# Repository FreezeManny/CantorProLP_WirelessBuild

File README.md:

# My Custom Cantor Pro LP Wireless Keyboard

This repository contains all the files and configuration for my personal build of the **Cantor Pro LP**, a 40% low-profile, hotswap, split ergonomic keyboard. This build is fully wireless, using Nice!Nano controllers running the ZMK firmware.

## Table of Contents

- [Hardware Components](#hardware-components)
- [PCB](#pcb)
- [Firmware (ZMK)](#firmware-zmk)
- [3D Printed Case](#3d-printed-case)
- [Build Notes](#build-notes)
- [Acknowledgements](#acknowledgements)

---

## Hardware Components

| Component | Item | Notes |
| :--- | :--- | :--- |
| **Keyboard Kit** | PCBs ordered from JLCPCB but | A kit can be sorced from 42. Keebs: [Cantor Pro LP Kit](https://42keebs.eu/shop/kits/pro-micro-based/cantor-pro-lp-40-low-profile-hotswap-split-ergo-kit/) |
| **Small Electronics** | 2x Push Button 6x2mm & 42x Kailh Choc V1 Hotswap Sockets | Ordered from aliExpress, not needed when buying a Kit |
| **Small Case Parts**| 4x M3 Heat insert, 4x M3 Screw | needed for securing PCB to case |
| **Controllers** | 2x Nice!Nano v2 (or alternative) | For wireless connectivity via Bluetooth. |
| **Batteries** | 2x 102050 LiPo (1000mAh) | One for each half. Fits perfectly with the custom case. |
| **Switches** | 42x Kailh Choc V1  | in my case: Sunset, waiting for sunrise |
| **Keycaps** | 42x Choc V1 Keycaps` | e.g., MBK Blank Choc Keycaps. |
| **Case** | Custom 3D Printed Case & Cover | Files are located in the `/case` directory. |

---
## PCB
The 42 Keebs Cantor was remixed to change the text of the keyboard and understand the layers. 
The Files are located in the `/pcb/` directory. 

## Firmware (ZMK)

This keyboard runs on the [ZMK Firmware](https://zmk.dev/docs), which is designed for wireless keyboards. 

### My Configuration

* **ZMK Config:** The main configuration files are located in the `/config/` directory.

### Configure, Build & Flash
* Configuration: Done using awesome [Keymap Editor](https://nickcoutsos.github.io/keymap-editor/)
* Build: standard Github Actions
* Flash: To Flash consult Microcontroller Documentation

---

## 3D Printed Case

This build uses a custom-designed 3D printed case and a friction fit travel cover to protect the keys.
It was built in Fusion360 and source files, as well as Step files are shared. (because STL sucks)
* **Files Location:** `/case`

Only one side is provided. To print the other half, mirror the files in the slicer. 

### Recommended Print Settings

* **Material:** Any, preferabbly in ABS/ASA/PETG due to better heat resistance
* **Outer Walls:** minimum of 3
* **Layer Height:** 0.2mm
* **Infill:** 15-20%
* **Supports:** Not required

---

## Build Notes

* **Fully Wireless:** This build is fully wireless and does **not** use a TRRS cable. The two halves communicate via Bluetooth. The TRRS jacks on the PCB are not installed.
* **Battery Placement:** The batteries are not placed underneath the controllers. They are placed under in the Case. Due to tight tolerances, trim the PCB pins flush
* **Pin Difficultys using NiceNano:** Due to the design of the PCB, when using the NiceNano, the 101 Pin has to be connected to the bottom row at an angle. Also on the right side of the keyboard, the left thumb key and the 5. key in Row 3 are swapped in the keymap. 

---

## Acknowledgements

* **Cantor Keyboard:** Diego Palacios
* **Cantor Pro LP Kit:** [42. Keebs](https://42keebs.eu/)
* **ZMK Firmware:** The ZMK contributors.

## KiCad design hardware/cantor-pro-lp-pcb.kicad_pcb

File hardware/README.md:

# Cantor Pro LP Keyboard

Cantor Pro LP (formerly known as Cantor Pro Frood) is based on the original Cantor Keyboard by Diego Palacios, with the following modifications:

* Supports more modern controllers instead of the Black Pill:
    * [42. Keebs Frood](https://42keebs.eu/shop/parts/controllers/frood-rp2040-pro-micro-controller/) ([GitHub repository](https://github.com/piit79/Frood)) RP2040-based controller
    * [nice!nano](https://nicekeyboards.com/nice-nano/) controller for a **wireless build**
* Adds battery contacts and a power switch
* It is a bit narrower thanks to the smaller controller
* Uses Kailh Choc V1 hotswap sockets
* Supports RGB underglow using 6x WS2812B / SK6812 5050 RGB modules
* Has holes for standoffs for use with a PCB switch plate or a [layered acrylic case](https://github.com/piit79/cantor/tree/main/case/cantor-pro-lp)

Cantor Pro LP kit is available for purchase at [42. Keebs](https://42keebs.eu/shop/kits/pro-micro-based/cantor-pro-lp-40-low-profile-hotswap-split-ergo-kit/).

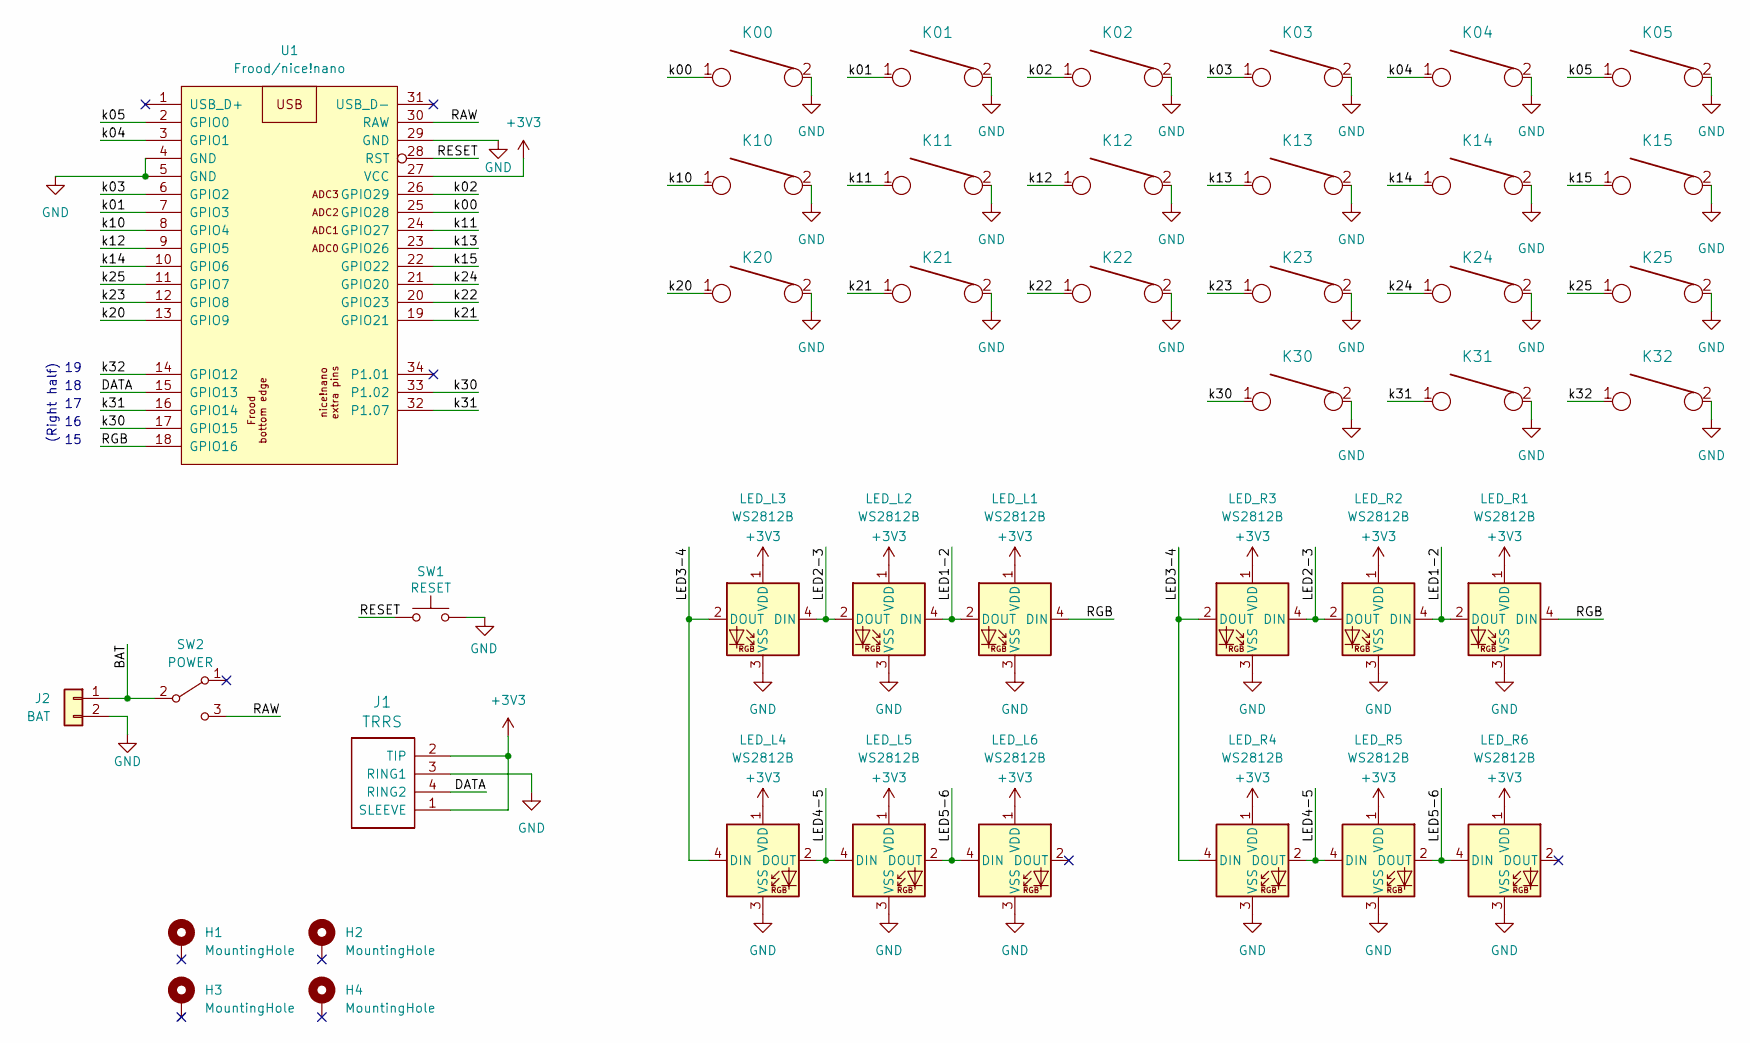
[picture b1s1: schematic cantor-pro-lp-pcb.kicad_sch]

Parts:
H1, H2, H3, H4: MountingHole; Standoff_Hole
J1: TRRS; TRRS-PJ-320A-reversible-symmetric
J2: BAT; ProMicro_Battery_Connector_Double_Sided_wide
K00, K01, K02, K03, K04, K05, K10, K11, K12, K13, K14, K15, K20, K21, K22, K23, K24, K25, K30, K31, K32: KEYSW; Kailh_socket_PG1350_reversible_cropped_pads_rounded_cutouts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
LED_L1, LED_L2, LED_L3, LED_L4, LED_L5, LED_L6: WS2812B; LED_WS2812B_PLCC4_5.0x5.0mm_P3.2mm_w_cutout
LED_R1, LED_R2, LED_R3, LED_R4, LED_R5, LED_R6: WS2812B; LED_WS2812B_PLCC4_5.0x5.0mm_P3.2mm_w_cutout
SW1: RESET; TACT_SWITCH_TVBP06
SW2: POWER; SW_SPDT_PCM12_double_sided_shifted_with_edge_cutouts
U1: Frood/nice!nano; Frood_nice-nano_PinHeader_2x12+5+3_P2.54mm_Dual_V-aligned

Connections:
+3V3: J1.1 (SLEEVE), J1.2 (TIP), LED_L1.1 (VDD), LED_L2.1 (VDD), LED_L3.1 (VDD), LED_L4.1 (VDD), LED_L5.1 (VDD), LED_L6.1 (VDD), LED_R1.1 (VDD), LED_R2.1 (VDD), LED_R3.1 (VDD), LED_R4.1 (VDD), LED_R5.1 (VDD), LED_R6.1 (VDD), U1.27 (VCC)
/BAT: J2.1, SW2.2 (B)
/DATA: J1.4 (RING2), U1.15 (GPIO13)
/LED1-2: LED_L1.2 (DOUT), LED_L2.4 (DIN), LED_R1.2 (DOUT), LED_R2.4 (DIN)
/LED2-3: LED_L2.2 (DOUT), LED_L3.4 (DIN), LED_R2.2 (DOUT), LED_R3.4 (DIN)
/LED3-4: LED_L3.2 (DOUT), LED_L4.4 (DIN), LED_R3.2 (DOUT), LED_R4.4 (DIN)
/LED4-5: LED_L4.2 (DOUT), LED_L5.4 (DIN), LED_R4.2 (DOUT), LED_R5.4 (DIN)
/LED5-6: LED_L5.2 (DOUT), LED_L6.4 (DIN), LED_R5.2 (DOUT), LED_R6.4 (DIN)
/RAW: SW2.3 (C), U1.30 (RAW)
/RESET: SW1.2, U1.28 (RST)
/RGB: LED_L1.4 (DIN), LED_R1.4 (DIN), U1.18 (GPIO16)
/k00: K00.1, U1.25 (GPIO28)
/k01: K01.1, U1.7 (GPIO3)
/k02: K02.1, U1.26 (GPIO29)
/k03: K03.1, U1.6 (GPIO2)
/k04: K04.1, U1.3 (GPIO1)
/k05: K05.1, U1.2 (GPIO0)
/k10: K10.1, U1.8 (GPIO4)
/k11: K11.1, U1.24 (GPIO27)
/k12: K12.1, U1.9 (GPIO5)
/k13: K13.1, U1.23 (GPIO26)
/k14: K14.1, U1.10 (GPIO6)
/k15: K15.1, U1.22 (GPIO22)
/k20: K20.1, U1.13 (GPIO9)
/k21: K21.1, U1.19 (GPIO21)
/k22: K22.1, U1.20 (GPIO23)
/k23: K23.1, U1.12 (GPIO8)
/k24: K24.1, U1.21 (GPIO20)
/k25: K25.1, U1.11 (GPIO7)
/k30: K30.1, U1.17 (GPIO15), U1.33 (P1.02)
/k31: K31.1, U1.16 (GPIO14), U1.32 (P1.07)
/k32: K32.1, U1.14 (GPIO12)
GND: J1.3 (RING1), J2.2, K00.2, K01.2, K02.2, K03.2, K04.2, K05.2, K10.2, K11.2, K12.2, K13.2, K14.2, K15.2, K20.2, K21.2, K22.2, K23.2, K24.2, K25.2, K30.2, K31.2, K32.2, LED_L1.3 (VSS), LED_L2.3 (VSS), LED_L3.3 (VSS), LED_L4.3 (VSS), LED_L5.3 (VSS), LED_L6.3 (VSS), LED_R1.3 (VSS), LED_R2.3 (VSS), LED_R3.3 (VSS), LED_R4.3 (VSS), LED_R5.3 (VSS), LED_R6.3 (VSS), SW1.1, U1.4 (GND), U1.5 (GND), U1.29 (GND)

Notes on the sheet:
(Right half)

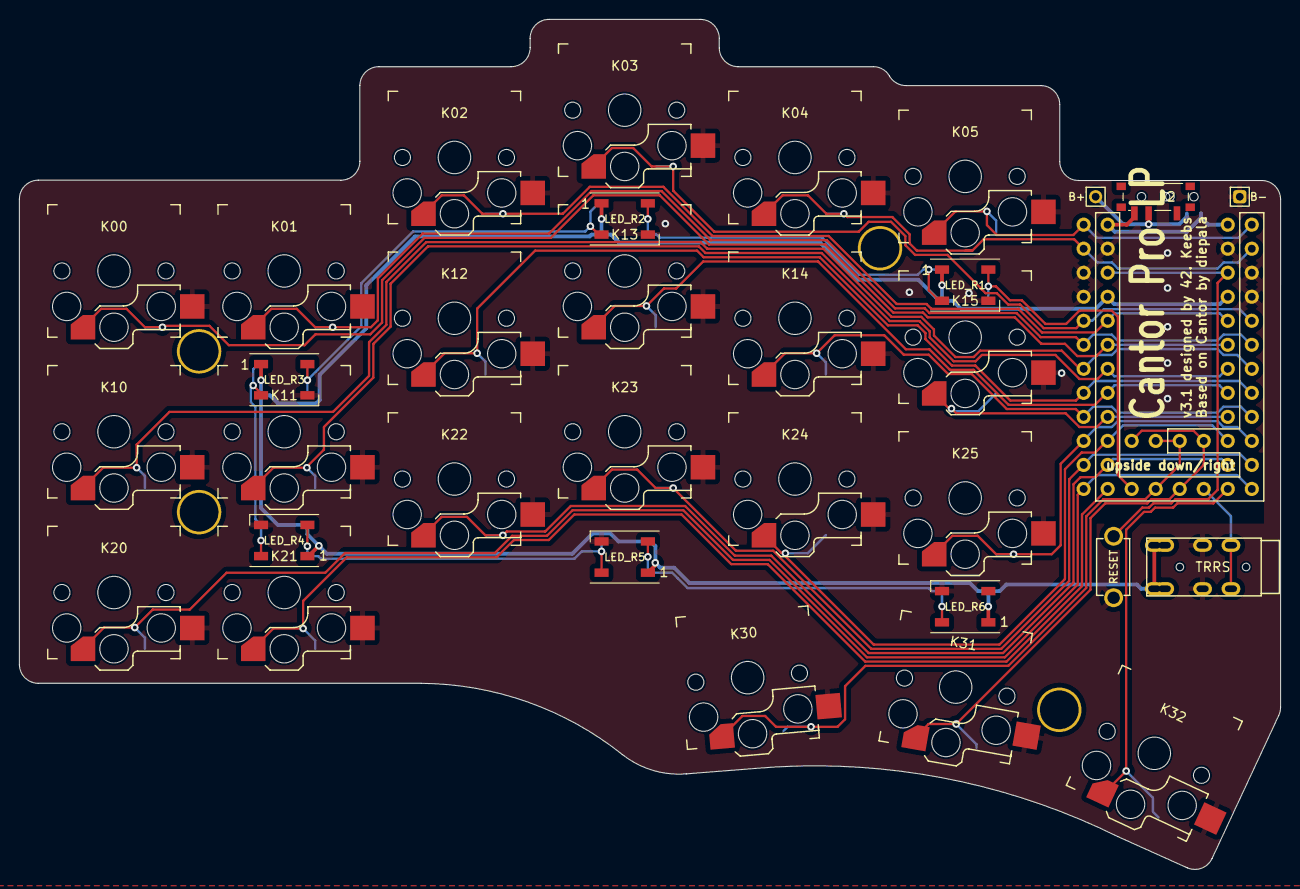
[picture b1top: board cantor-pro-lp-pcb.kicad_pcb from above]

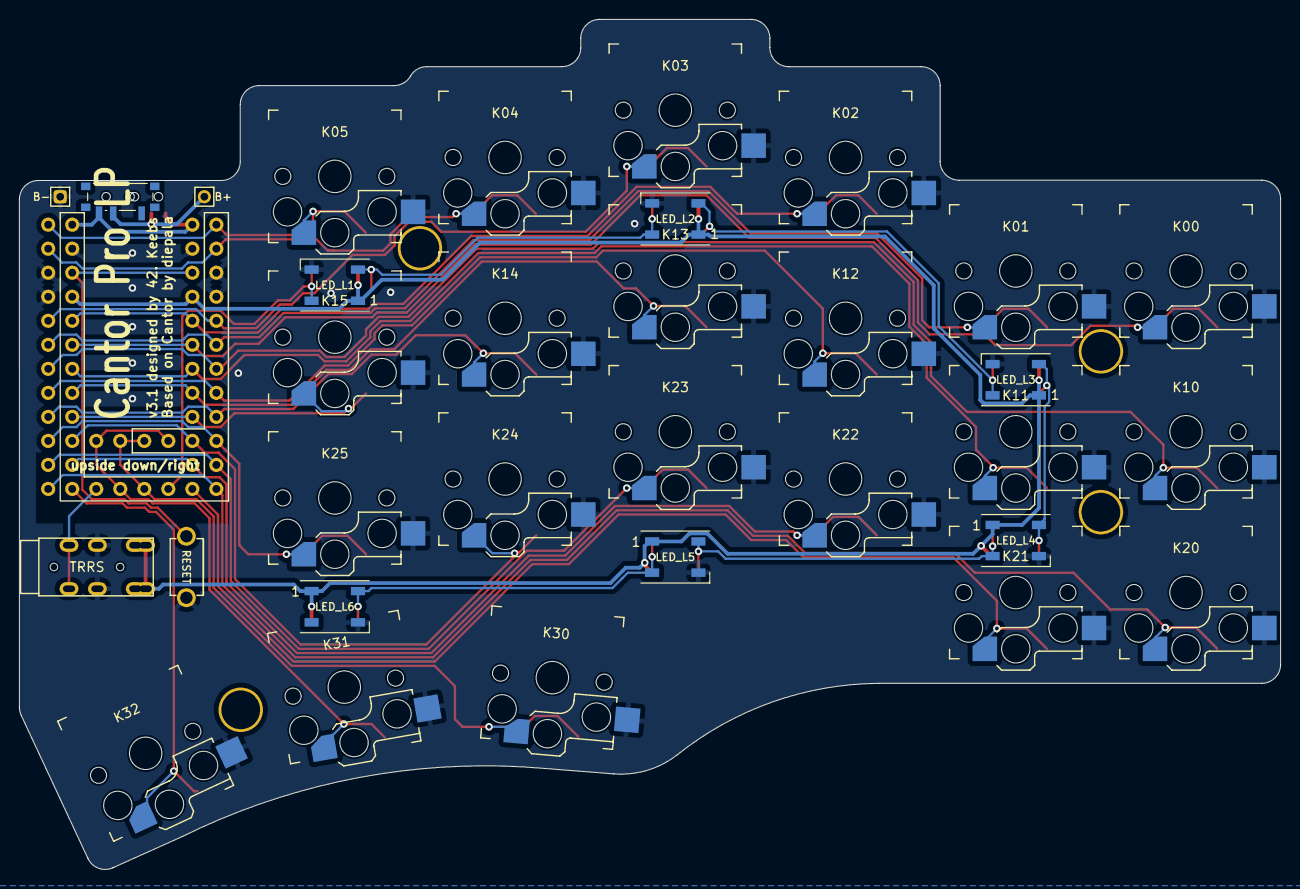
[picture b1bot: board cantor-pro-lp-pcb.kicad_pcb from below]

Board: 2 copper layers, 133.4 x 89.9 mm, 42 parts (6 on the bottom side), 33 nets.

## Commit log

2025-07-16 Initial User Config.
2025-07-24 Updated corne.keymap
2025-07-24 Added first Config Example
2025-07-24 added delete behind shift backspace
2025-08-30 Added Hardware
2025-08-31 Custom Message
2025-09-02 Updated Structure
2025-09-02 Reverse
2025-09-02 Rename back
2025-09-02 Added Caldera Default Config
2025-09-02 Added Layout Info.json
2025-09-02 Added second half
2025-09-02 Changed Info Path
2025-09-02 Updated layout and overlay. Still lots of work to do
2025-09-02 Updated Switch Map
2025-09-02 Added Correct Keyboard Switch Mapping
2025-09-02 Added KSCAN GPIOs to Layout
2025-09-02 Changed Paths to (hopefully) correct build path
2025-09-02 Moved Keymap back out
2025-09-02 Added Back cantor conf
2025-09-02 Comma format change
2025-09-02 Revert Back Config
2025-09-02 Added Comments to new File
2025-09-02 Fixed Syntax
2025-09-02 Gemini Update
2025-09-02 Changed Spaces
2025-09-02 Added Matrix Import
2025-09-02 Updated-parameter
2025-09-02 Added Back comment
2025-09-02 Try adding back more comments
2025-09-02 Changed Comment position
2025-09-18 Updated Layout as well as keymap
2025-09-18 Updated Naming
2025-09-18 Updated transform
2025-09-18 Removed custom Configs
2025-09-18 Added Physical Layout
2025-09-18 Update Imports
2025-09-18 Updated Input
2025-09-18 Wrapped negative numbers
2025-09-18 removed info.json for test
2025-09-18 Added info back
2025-09-18 Move back but with AI Scaling
2025-09-18 Adjusted info row and column
2025-09-18 Layout update
2025-09-18 hotfix
2025-09-18 AI Update and fix
2025-09-18 AI Update
2025-09-18 Trying to push
2025-09-18 push
2025-09-18 Updated Keymap
2025-09-18 Updated cantor.keymap
2025-09-19 Reversed Right Mapping due to Pin differences
2025-09-20 moved backspace key
2025-09-24 moved around postioning of f keys to match the regular number row
2025-09-24 added printscreen and page up and down
2025-09-24 fixed key that needed testing
2025-09-24 shifted bits around
2025-09-29 Added Backslash and forward Slash
2025-10-06 Added direct macros for german keys
2025-10-07 Added Readme
2025-10-07 Add PCB section to Table of Contents
2025-10-07 Renamed hardware to PCB
2025-10-07 Added 3D Print Files as well as images to the readme
2025-11-03 Added macros
2025-11-03 added ShiftSlash
2025-11-03 Modified Slashes and Pipes
2025-11-03 BugFix
2025-11-07 Fixed Offset German Keys
2025-11-07 Fixed Missing None
2025-12-10 Added Media Keys
2025-12-10 modified media keys
2025-12-21 Updated Pin Differences in keymap
2025-12-21 Restore Shift Slash
2025-12-21 Moved Pipe for proper shiftslash
2025-12-21 Added Colemak switching
2025-12-21 Updated layer Shift
2025-12-21 Updated right Overlay
2026-01-17 Swapped Num and F row for curling fingers for numbers
